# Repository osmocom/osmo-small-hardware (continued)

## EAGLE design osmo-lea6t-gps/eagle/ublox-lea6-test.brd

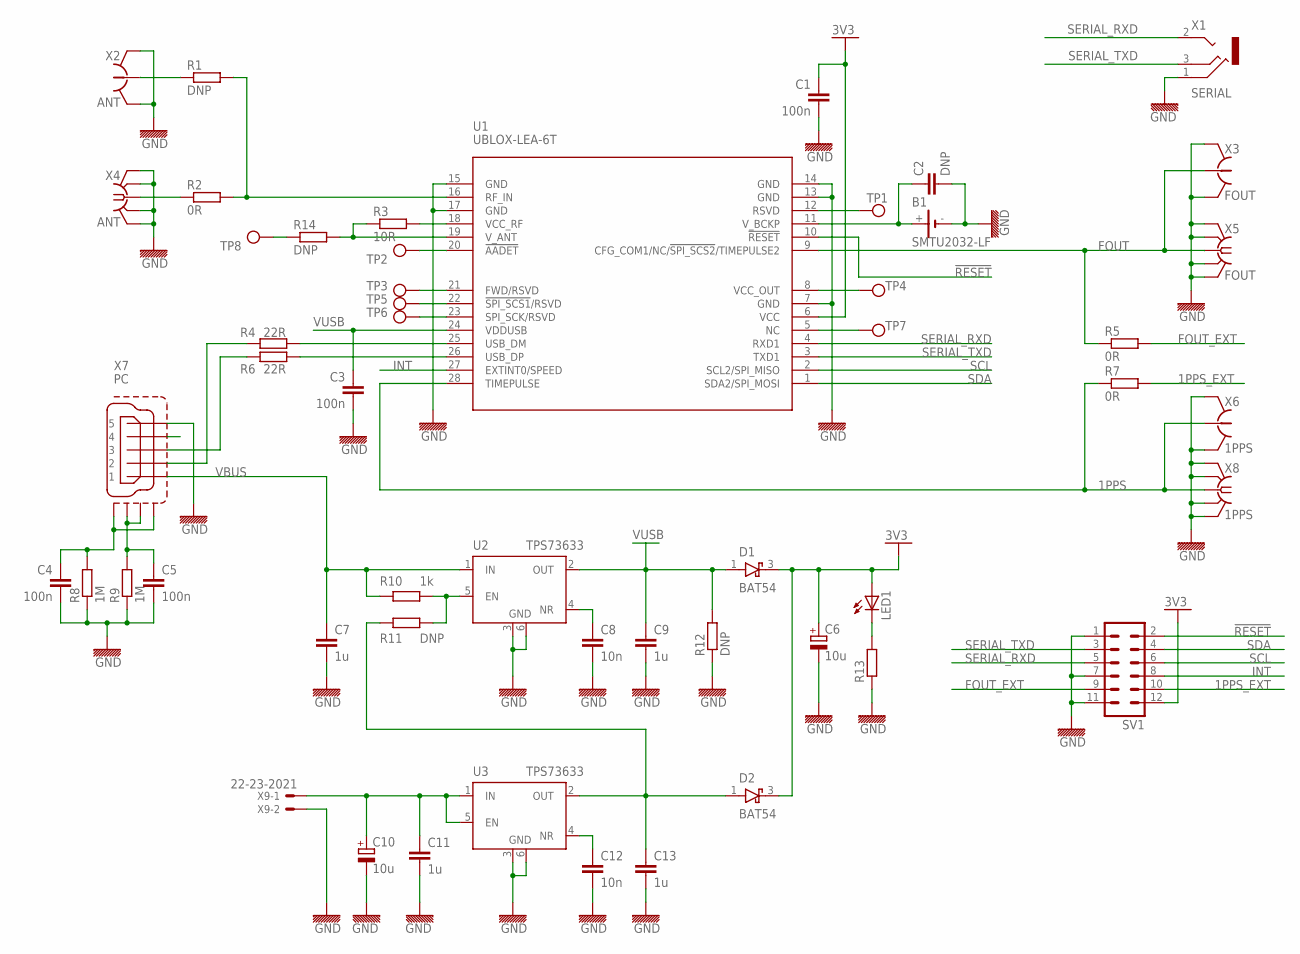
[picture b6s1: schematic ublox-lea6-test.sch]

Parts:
B1: SMTU2032-LF; SMTU2032
C1, C3, C4, C5: 100n; 0603
C2: DNP; 0603
C6, C10: 10u; A/3216-18R
C7, C9, C11, C13: 1u; 0603
C8, C12: 10n; 0603
D1, D2: BAT54; SOT23
LED1: LEDSML0603; SML0603
R1, R11, R12, R14: DNP; 0603
R2, R5, R7: 0R; 0603
R3: 10R; 0603
R4, R6: 22R; 0603
R8, R9: 1M; 0603
R10: 1k; 0603
R13: R-EU_0603; 0603
SV1: MA06-2
TP1, TP2, TP3, TP4, TP5, TP6, TP7, TP8: TESTPAD; TP_1X1
U1: UBLOX-LEA-6T; UBLOX-LEA-6
U2, U3: TPS73633; SOT223-6
X1: SERIAL; JACK2.5_SJ-2523
X2: ANT; HRS_UFL
X3: FOUT; HRS_UFL
X4: ANT; SMA-F-S-EDGE
X5: FOUT; SMA-F-S-EDGE
X6: 1PPS; HRS_UFL
X7: PC; UX60-MB-5ST
X8: 1PPS; SMA-F-S-EDGE
X9: 22-23-2021

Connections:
1PPS: R7.1, U1.28 (TIMEPULSE), X6.SIG (1), X8.C (1)
1PPS_EXT: R7.2, SV1.10
3V3: C1.1, C6.+, D1.3 (C), D2.3 (C), LED1.A, SV1.12, U1.6 (VCC)
!RESET: SV1.2, U1.10 (!RESET)
FOUT: R5.1, U1.9 (CFG_COM1/NC/!SPI_SCS2!/TIMEPULSE2), X3.SIG (1), X5.C (1)
FOUT_EXT: R5.2, SV1.9
GND: B1.-, C1.2, C2.2, C3.2, C4.2, C5.2, C6.-, C7.2, C8.2, C9.2, C10.-, C11.2, C12.2, C13.2, R8.1, R9.1, R12.1, R13.1, SV1.1, SV1.7, SV1.11, U1.7 (GND), U1.13 (GND), U1.14 (GND), U1.15 (GND), U1.17 (GND), U2.3 (GND), U2.6 (GND1), U3.3 (GND), U3.6 (GND1), X1.1 (RING), X2.GND@1 (GND), X2.GND@2 (GND), X3.GND@1 (GND), X3.GND@2 (GND), X4.BG1 (GND), X4.BG2 (GND), X4.TG1 (GND), X4.TG2 (GND), X5.BG1 (GND), X5.BG2 (GND), X5.TG1 (GND), X5.TG2 (GND), X6.GND@1 (GND), X6.GND@2 (GND), X7.5, X8.BG1 (GND), X8.BG2 (GND), X8.TG1 (GND), X8.TG2 (GND), X9.2
INT: SV1.8, U1.27 (EXTINT0/SPEED)
unnamed: R2.1, X4.C (1)
unnamed: C4.1, R8.2, X7.M1 (S1), X7.M4 (S4)
unnamed: R4.2, U1.25 (USB_DM)
unnamed: R6.2, U1.26 (USB_DP)
unnamed: R3.2, U1.18 (VCC_RF)
unnamed: R3.1, R14.2, U1.19 (V_ANT)
unnamed: TP3.TP, U1.21 (FWD/RSVD)
unnamed: TP2.TP, U1.20 (!AADET)
unnamed: TP5.TP, U1.22 (!SPI_SCS1!/RSVD)
unnamed: TP6.TP, U1.23 (SPI_SCK/RSVD)
unnamed: R6.1, X7.3
unnamed: R4.1, X7.2
unnamed: C8.1, U2.4 (NR)
unnamed: TP1.TP, U1.12 (RSVD)
unnamed: B1.+, C2.1, U1.11 (V_BCKP)
unnamed: R1.1, X2.SIG (1)
unnamed: TP4.TP, U1.8 (VCC_OUT)
unnamed: TP7.TP, U1.5 (NC)
unnamed: R1.2, R2.2, U1.16 (RF_IN)
unnamed: C5.1, R9.2, X7.M2 (S2), X7.M3 (S3)
unnamed: C10.+, C11.1, U3.1 (IN), U3.5 (EN), X9.1
unnamed: C12.1, U3.4 (NR)
unnamed: C13.1, D2.1 (A), R11.1, U3.2 (OUT)
unnamed: R10.2, R11.2, U2.5 (EN)
unnamed: LED1.C, R13.2
unnamed: R14.1, TP8.TP
SCL: SV1.6, U1.2 (SCL2/SPI_MISO)
SDA: SV1.4, U1.1 (SDA2/SPI_MOSI)
SERIAL_RXD: SV1.5, U1.4 (RXD1), X1.2 (TIP)
SERIAL_TXD: SV1.3, U1.3 (TXD1), X1.3 (MIDDLE)
VBUS: C7.1, R10.1, U2.1 (IN), X7.1
VUSB: C3.1, C9.1, D1.1 (A), R12.2, U1.24 (VDDUSB), U2.2 (OUT)

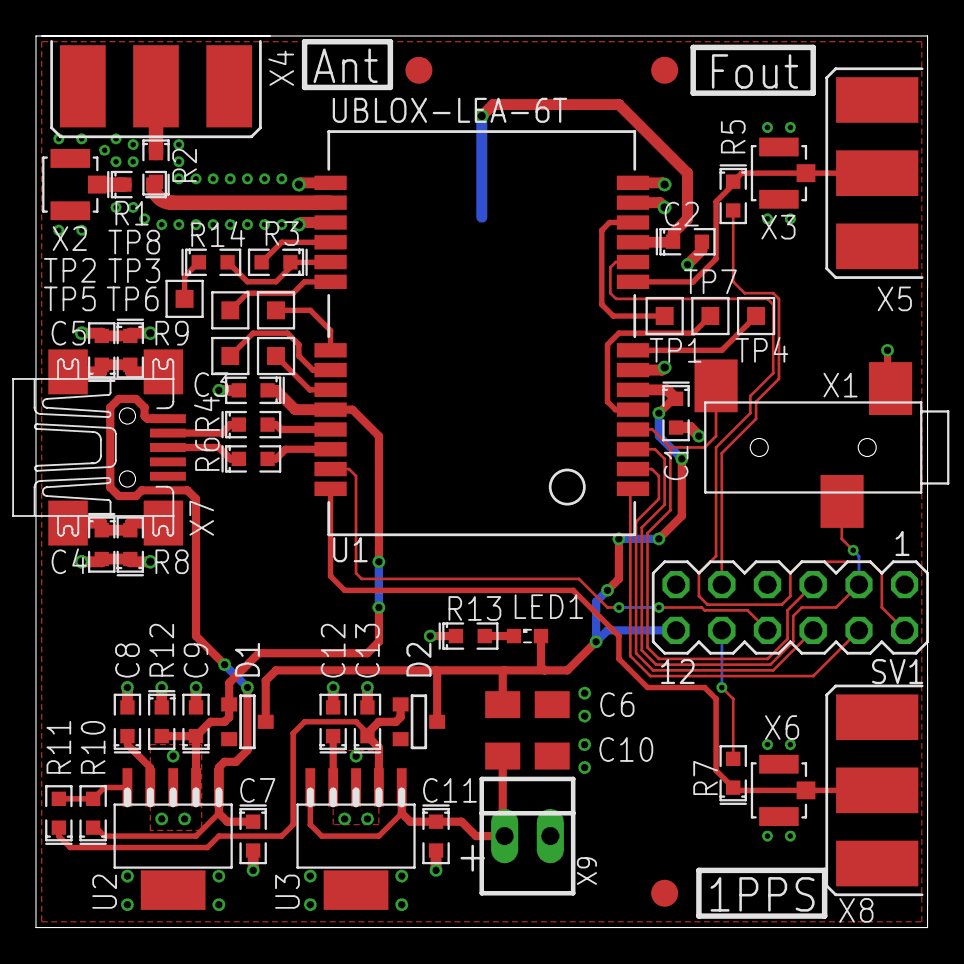
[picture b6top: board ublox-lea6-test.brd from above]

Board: 2 copper layers, 49.5 x 49.5 mm, 55 parts (1 on the bottom side), 40 nets.

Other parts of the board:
U$30, U$31, U$32: VISION_REF15

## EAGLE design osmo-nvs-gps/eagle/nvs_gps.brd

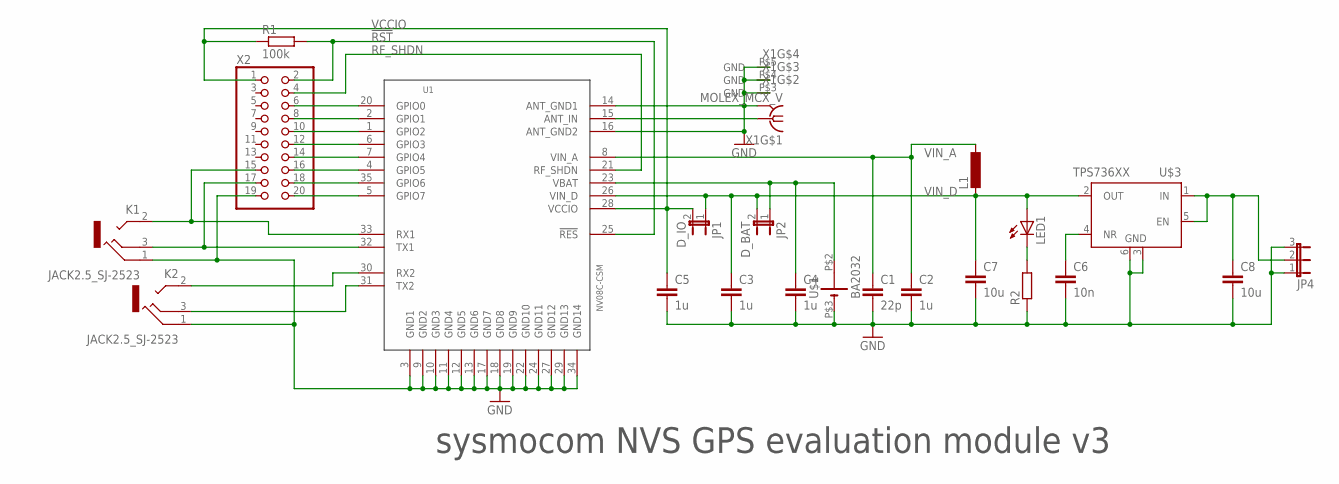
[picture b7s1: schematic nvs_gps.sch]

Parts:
C1: 22p; C0402K
C2, C3, C4, C5: 1u; C0603
C6: 10n; C0603
C7, C8: 10u; C0603
JP1: D_IO; JP1
JP2: D_BAT; JP1
JP4: JP2E; JP2
K1, K2: JACK2.5_SJ-2523
L1: L-EU0603; 0603
LED1: LED0603; LED-0603
R1: 100k; R0603
R2: R-EU_R0603; R0603
U1: NV08C-CSM
U$1: BA2032; BA2023-ND
U$3: TPS736XX; SOT223-6
X1: MOLEX_MCX_V
X2: PINHD-2X10; 2X10

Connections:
!RST: R1.2, U1.25 (!RES), X2.2
GND: C1.2, C2.2, C3.2, C4.2, C5.2, C6.2, C7.2, C8.2, JP4.1, JP4.3, K1.1 (RING), K2.1 (RING), R2.1, U1.3 (GND1), U1.9 (GND2), U1.10 (GND3), U1.11 (GND4), U1.12 (GND5), U1.13 (GND6), U1.14 (ANT_GND1), U1.16 (ANT_GND2), U1.17 (GND7), U1.18 (GND8), U1.19 (GND9), U1.22 (GND10), U1.24 (GND11), U1.27 (GND12), U1.29 (GND13), U1.34 (GND14), U$1.P$3 (-), U$3.3 (GND), U$3.6 (GND1), X1.P$2 (GND), X1.P$3 (GND), X1.P$4 (GND), X1.P$5 (GND), X2.19
K1: K1.2 (TIP), U1.33 (RX1), X2.15
unnamed: C6.1, U$3.4 (NR)
unnamed: U1.5 (GPIO7), X2.20
unnamed: U1.35 (GPIO6), X2.18
unnamed: K1.3 (MIDDLE), U1.32 (TX1), X2.17
unnamed: K2.3 (MIDDLE), U1.31 (TX2)
unnamed: K2.2 (TIP), U1.30 (RX2)
unnamed: C4.1, JP2.1, U1.23 (VBAT), U$1.P$2 (+)
unnamed: U1.4 (GPIO5), X2.16
unnamed: U1.7 (GPIO4), X2.14
unnamed: U1.6 (GPIO3), X2.12
unnamed: U1.1 (GPIO2), X2.10
unnamed: U1.2 (GPIO1), X2.8
unnamed: U1.20 (GPIO0), X2.6
unnamed: LED1.C, R2.2
RF: U1.15 (ANT_IN), X1.P$1 (1)
RF_SHDN: U1.21 (RF_SHDN), X2.4
VCCIO: C5.1, JP1.2, R1.1, U1.28 (VCCIO), X2.1
VIN_A: C1.1, C2.1, L1.1, U1.8 (VIN_A)
VIN_D: C3.1, C7.1, JP1.1, JP2.2, L1.2, LED1.A, U1.26 (VIN_D), U$3.2 (OUT)
V_IN: C8.1, JP4.2, U$3.1 (IN), U$3.5 (EN)

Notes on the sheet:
sysmocom NVS GPS evaluation module v3

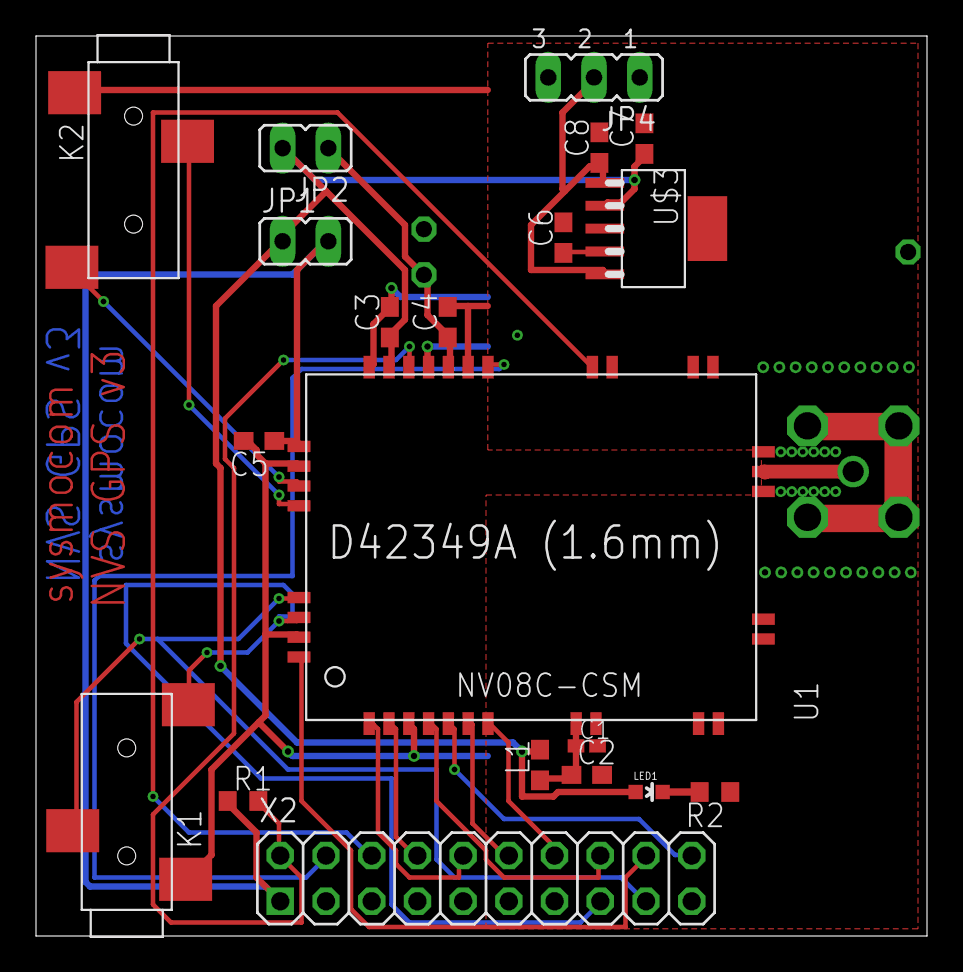
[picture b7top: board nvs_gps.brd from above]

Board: 2 copper layers, 49.5 x 50.0 mm, 22 parts (1 on the bottom side), 23 nets.
